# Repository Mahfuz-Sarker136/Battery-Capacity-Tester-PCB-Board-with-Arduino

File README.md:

# Battery-Capacity-Tester-PCB-Board-with-Arduino
Battery Capacity Tester which measures mAh by controlled discharge of lithium ion battery .It works with Arduino.
# Battery Capacity Tester — Arduino

A simple battery capacity tester that measures the 
capacity of a lithium-ion battery in mAh using 
controlled discharge through a resistor.

## How It Works

The battery is discharged through a load resistor (R1 = 10Ω) 
controlled by an NMOS transistor (Q2). The Arduino monitors 
the battery voltage and calculates the discharged capacity 
over time. LED (with R2= 330Ω) indicates that test is running.

## Components

Component 
Arduino Uno ,  Q2(IRFZ44N),  R1(10Ω)  , R2 R3(330Ω) , LED(5mm) 

## Schematic

See `Schematic.pdf`

## PCB

Designed in KiCad 9.0.7

## Output

Capacity result displayed on Serial Monitor in mAh.

## License

MIT

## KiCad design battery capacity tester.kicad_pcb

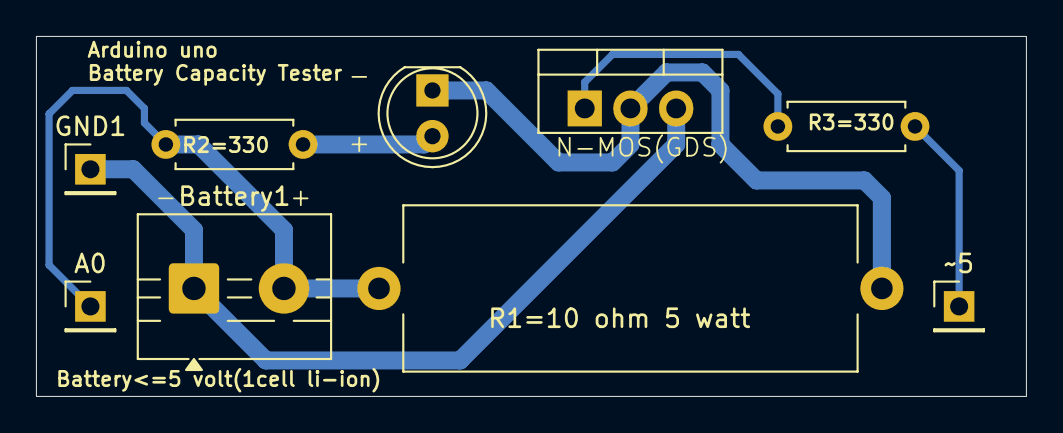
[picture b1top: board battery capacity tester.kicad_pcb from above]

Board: 2 copper layers, 55.0 x 20.0 mm, 8 parts (0 on the bottom side), 5 nets.

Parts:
A0: Conn_01x01; PinHeader_1x01_P2.54mm_Vertical
Battery1: Screw_Terminal_01x02; TerminalBlock_MaiXu_MX126-5.0-02P_1x02_P5.00mm
D1: LED; LED_D5.0mm
GND1: Conn_01x01; PinHeader_1x01_P2.54mm_Vertical
Q2: Q_NMOS_GDS; TO-220-3_Vertical
R1: 10; R_Axial_Power_L25.0mm_W9.0mm_P27.94mm
R2, R3: 330; R_Axial_DIN0207_L6.3mm_D2.5mm_P7.62mm_Horizontal

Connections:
GND: Battery1.1, GND1.1, Q2.3 (S)
unnamed: A0.1, Battery1.2, R1.1, R2.1
unnamed: D1.2 (A), R2.2
unnamed: D1.1 (K), Q2.2 (D), R1.2
unnamed: Q2.1 (G), R3.2
